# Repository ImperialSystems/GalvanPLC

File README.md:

# GalvanPLC
Galvan PLC es una adaptación de la plataforma Arduino al ámbito industrial, dicho de forma más clara es una imitación de los PLC. El hardware es completamente abierto y está bajo licencia GPL V2. El PCB fue diseñado en KiCAD con solo una capa y pensado para que pueda montarse tanto de forma casera como de forma profesional. Cuenta con 4 salidas digitales del tipo relay, 3 salidas analógicas de 0-5V, 2 entradas analógicas de 10V, 2 entradas analógicas de 4-20mA y 5 entradas digitales de 24V. Puede alimentarse entre 8VDC y 30VDC. Posee conexión USB y comunicación I2C. Es compatible con Soapbox Snap, OpenPLC, LDmicro y Arduino IDE, entre otros.

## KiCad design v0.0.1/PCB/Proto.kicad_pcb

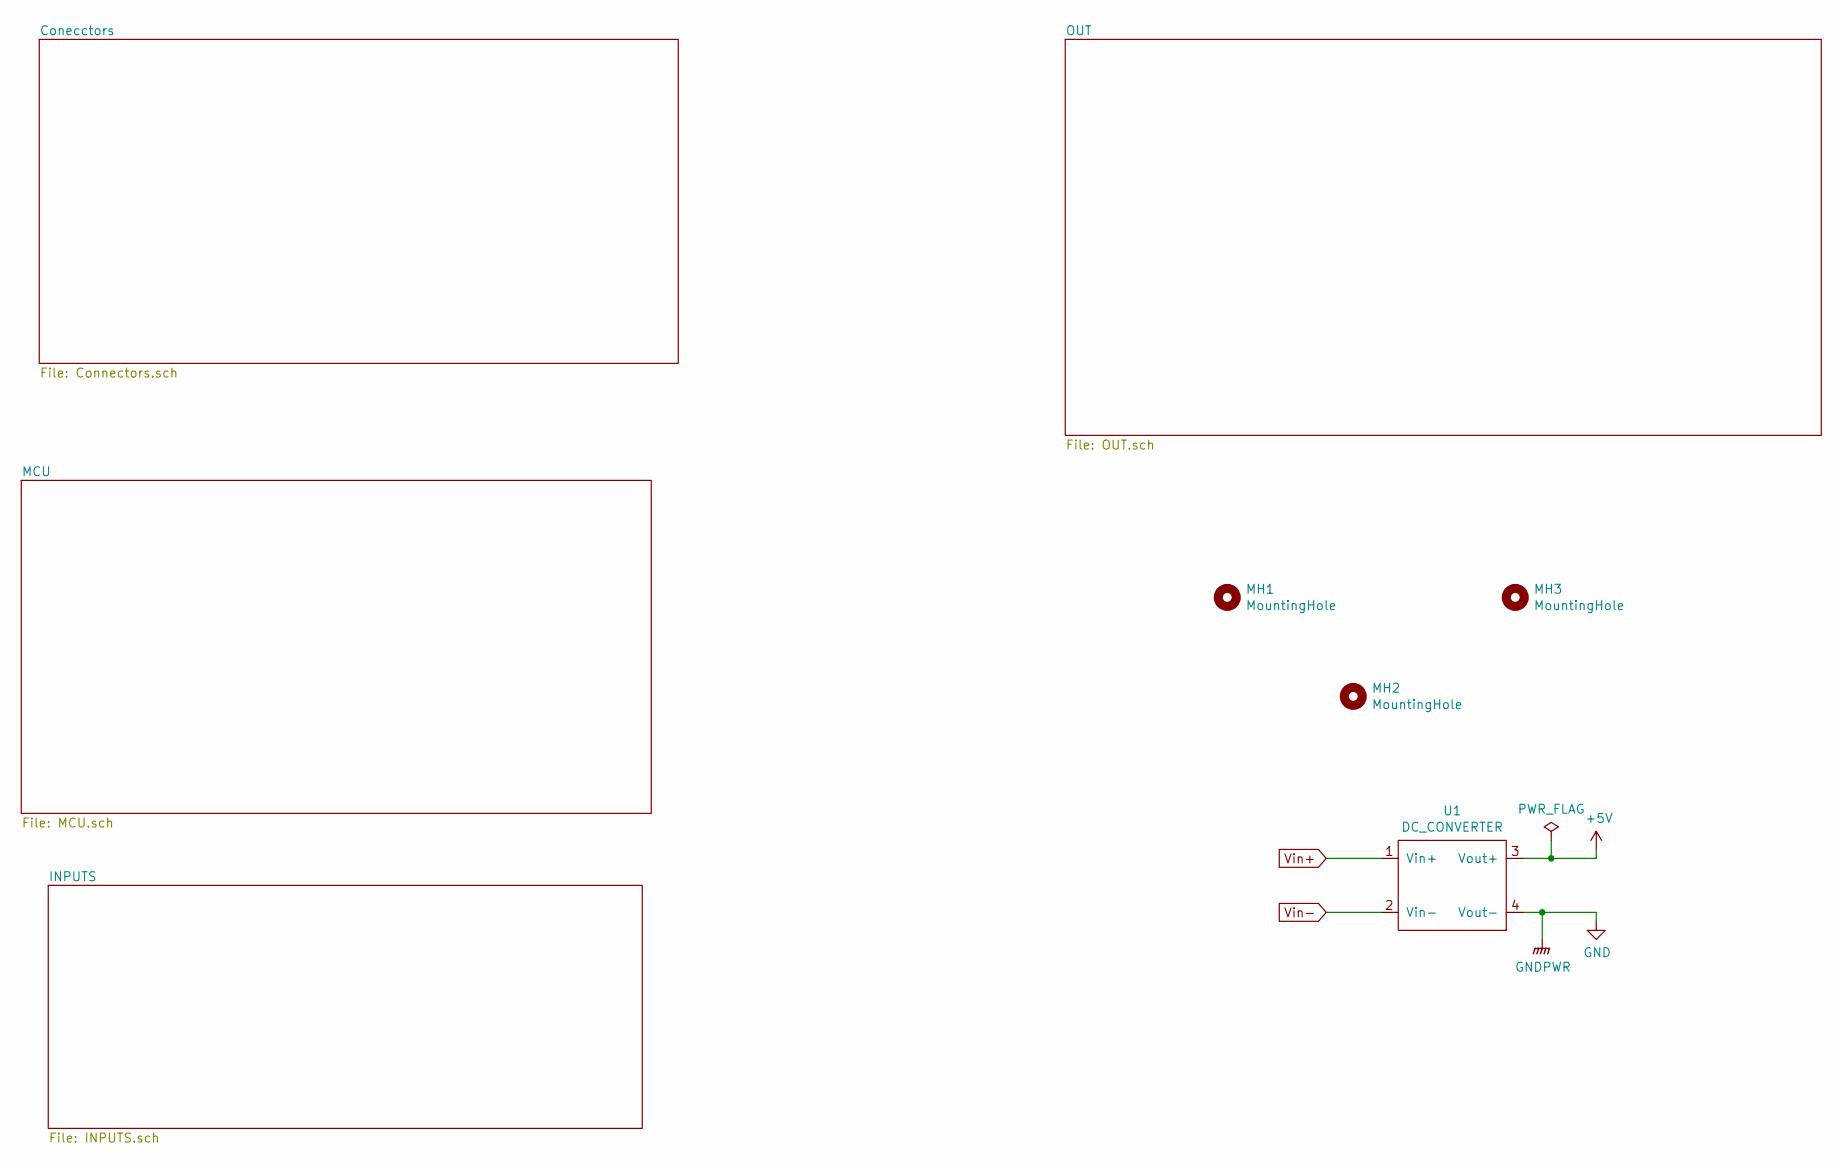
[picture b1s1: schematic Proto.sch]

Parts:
MH1, MH2, MH3: MountingHole; MountingHole_5mm
U1: DC_CONVERTER; Module_LM2596

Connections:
+5V: U1.3 (Vout+); also elsewhere on the board
GND: U1.4 (Vout-); also elsewhere on the board

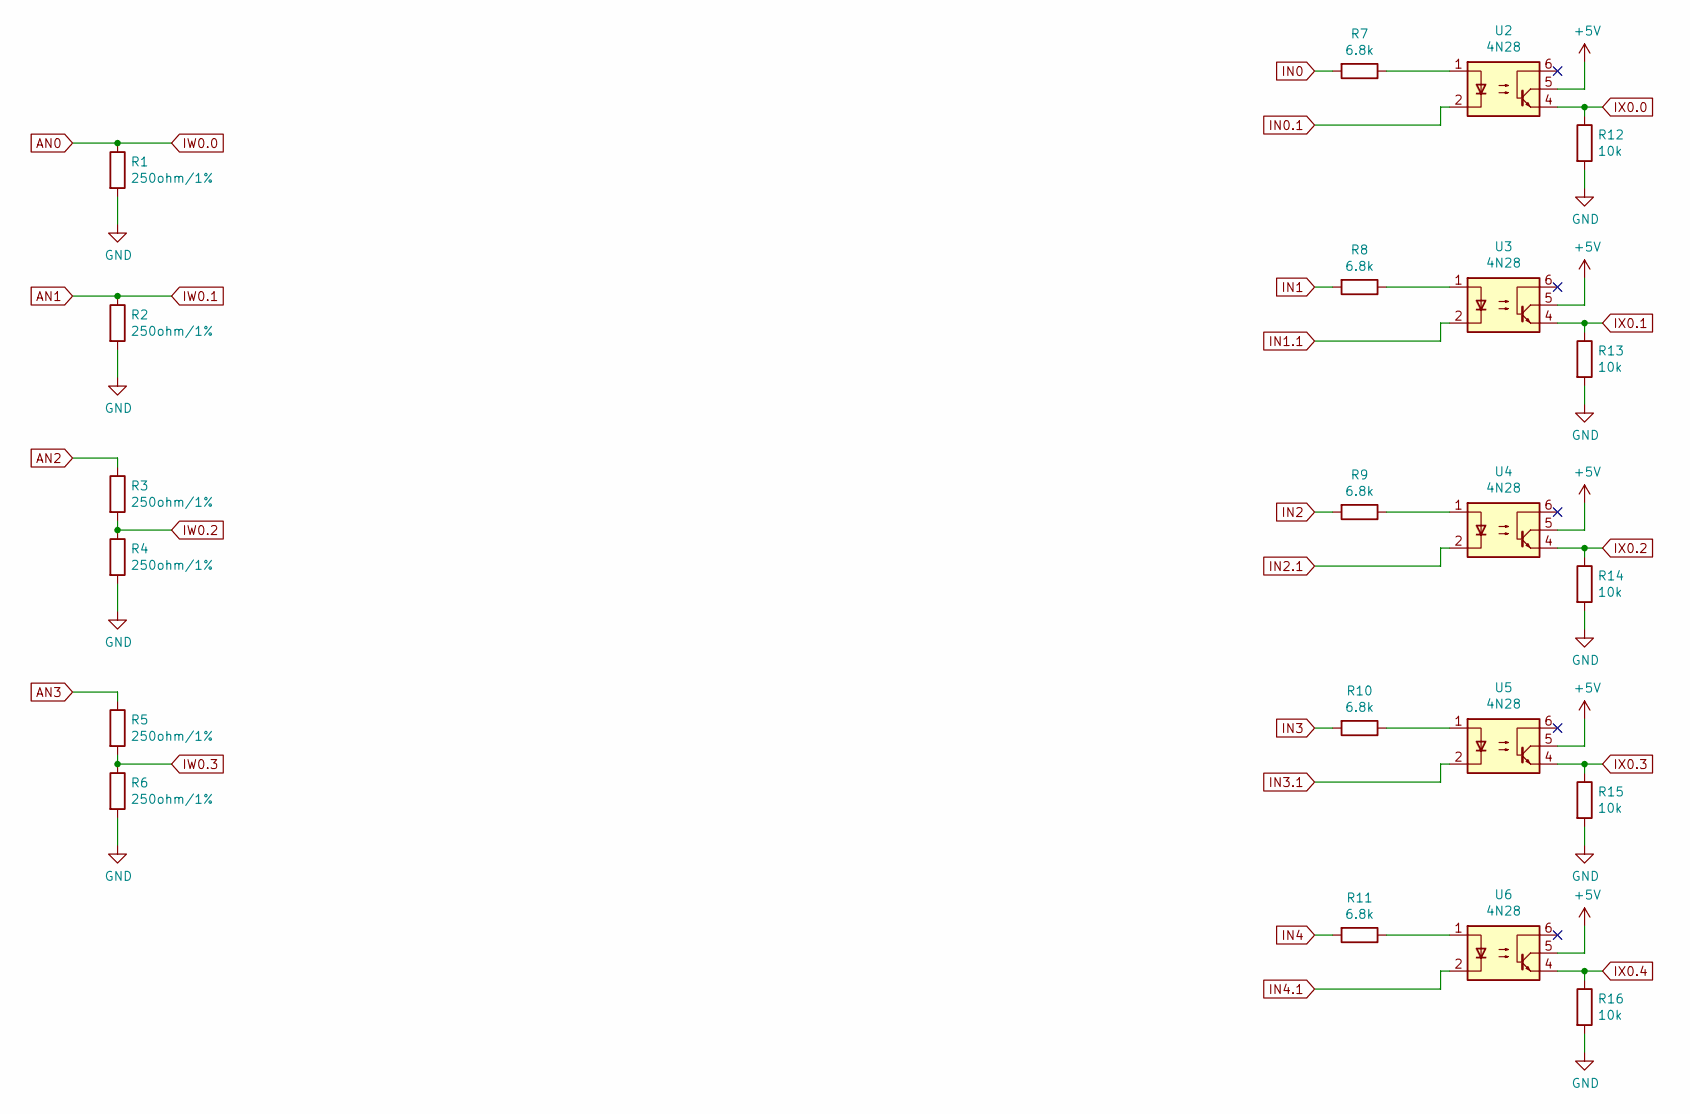
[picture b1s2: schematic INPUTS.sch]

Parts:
R1, R2, R4, R6: 250ohm/1%; R_Axial_DIN0207_L6.3mm_D2.5mm_P15.24mm_Horizontal
R3, R5: 250ohm/1%; R_Axial_DIN0207_L6.3mm_D2.5mm_P10.16mm_Horizontal
R7, R8, R9, R10, R11: 6.8k; R_Axial_DIN0207_L6.3mm_D2.5mm_P15.24mm_Horizontal
R12, R13, R14, R15, R16: 10k; R_Axial_DIN0207_L6.3mm_D2.5mm_P15.24mm_Horizontal
U2, U3, U4, U5, U6: 4N28; DIP-6_W7.62mm

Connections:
+5V: U2.5, U3.5, U4.5, U5.5, U6.5; also elsewhere on the board
AN0: R1.1; also elsewhere on the board
AN1: R2.1; also elsewhere on the board
AN2: R3.1; also elsewhere on the board
AN3: R5.1; also elsewhere on the board
GND: R1.2, R2.2, R4.2, R6.2, R12.2, R13.2, R14.2, R15.2, R16.2; also elsewhere on the board
IN0: R7.2; also elsewhere on the board
IN0.1: U2.2; also elsewhere on the board
IN1: R8.2; also elsewhere on the board
IN1.1: U3.2; also elsewhere on the board
IN2: R9.2; also elsewhere on the board
IN2.1: U4.2; also elsewhere on the board
IN3: R10.2; also elsewhere on the board
IN3.1: U5.2; also elsewhere on the board
IN4: R11.2; also elsewhere on the board
IN4.1: U6.2; also elsewhere on the board
IW0.2: R3.2, R4.1; also elsewhere on the board
IW0.3: R5.2, R6.1; also elsewhere on the board
IX0.0: R12.1, U2.4; also elsewhere on the board
IX0.1: R13.1, U3.4; also elsewhere on the board
IX0.2: R14.1, U4.4; also elsewhere on the board
IX0.3: R15.1, U5.4; also elsewhere on the board
IX0.4: R16.1, U6.4; also elsewhere on the board
unnamed: R7.1, U2.1
unnamed: R8.1, U3.1
unnamed: R9.1, U4.1
unnamed: R10.1, U5.1
unnamed: R11.1, U6.1

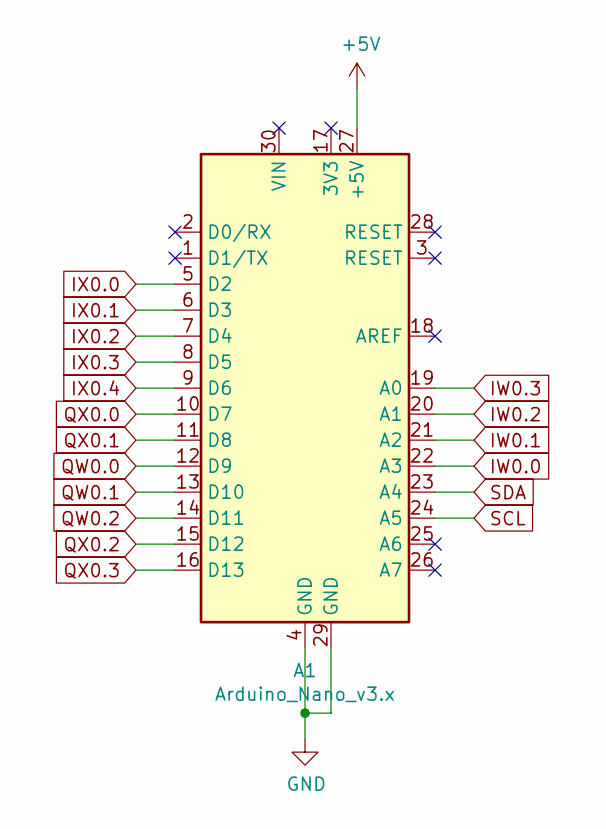
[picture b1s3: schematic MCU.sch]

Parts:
A1: Arduino_Nano_v3.x; Arduino_Nano

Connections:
+5V: A1.27 (+5V); also elsewhere on the board
AN0: A1.22 (A3); also elsewhere on the board
AN1: A1.21 (A2); also elsewhere on the board
GND: A1.4 (GND), A1.29 (GND); also elsewhere on the board
IW0.2: A1.20 (A1); also elsewhere on the board
IW0.3: A1.19 (A0); also elsewhere on the board
IX0.0: A1.5 (D2); also elsewhere on the board
IX0.1: A1.6 (D3); also elsewhere on the board
IX0.2: A1.7 (D4); also elsewhere on the board
IX0.3: A1.8 (D5); also elsewhere on the board
IX0.4: A1.9 (D6); also elsewhere on the board
QW0.0: A1.12 (D9); also elsewhere on the board
QW0.1: A1.13 (D10); also elsewhere on the board
QW0.2: A1.14 (D11); also elsewhere on the board
QX0.0: A1.10 (D7); also elsewhere on the board
QX0.1: A1.11 (D8); also elsewhere on the board
QX0.2: A1.15 (D12); also elsewhere on the board
QX0.3: A1.16 (D13); also elsewhere on the board
SCL: A1.24 (A5); also elsewhere on the board
SDA: A1.23 (A4); also elsewhere on the board

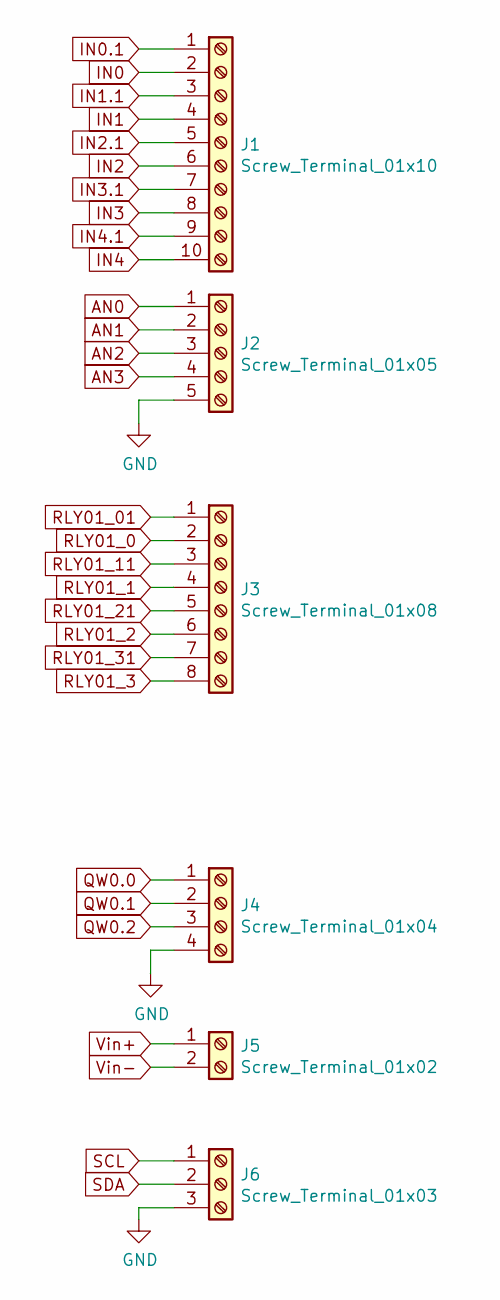
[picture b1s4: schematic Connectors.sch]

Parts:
J1: Screw_Terminal_01x10; TerminalBlock_Phoenix_MKDS-1,5-10-5.08_1x10_P5.08mm_Horizon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
J2: Screw_Terminal_01x05; TerminalBlock_Phoenix_MKDS-1,5-5_1x05_P5.00mm_Horizontal
J3: Screw_Terminal_01x08; TerminalBlock_Phoenix_MKDS-1,5-8_1x08_P5.00mm_Horizontal
J4: Screw_Terminal_01x04; TerminalBlock_Phoenix_MKDS-1,5-4_1x04_P5.00mm_Horizontal
J5: Screw_Terminal_01x02; TerminalBlock_Phoenix_MKDS-1,5-2_1x02_P5.00mm_Horizontal
J6: Screw_Terminal_01x03; TerminalBlock_Phoenix_MKDS-1,5-3_1x03_P5.00mm_Horizontal

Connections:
AN0: J2.1; also elsewhere on the board
AN1: J2.2; also elsewhere on the board
AN2: J2.3; also elsewhere on the board
AN3: J2.4; also elsewhere on the board
GND: J2.5, J4.4, J6.3; also elsewhere on the board
IN0: J1.2; also elsewhere on the board
IN0.1: J1.1; also elsewhere on the board
IN1: J1.4; also elsewhere on the board
IN1.1: J1.3; also elsewhere on the board
IN2: J1.6; also elsewhere on the board
IN2.1: J1.5; also elsewhere on the board
IN3: J1.8; also elsewhere on the board
IN3.1: J1.7; also elsewhere on the board
IN4: J1.10; also elsewhere on the board
IN4.1: J1.9; also elsewhere on the board
QW0.0: J4.1; also elsewhere on the board
QW0.1: J4.2; also elsewhere on the board
QW0.2: J4.3; also elsewhere on the board
RLY01_0: J3.2; also elsewhere on the board
RLY01_01: J3.1; also elsewhere on the board
RLY01_1: J3.4; also elsewhere on the board
RLY01_2: J3.6; also elsewhere on the board
RLY01_3: J3.8; also elsewhere on the board
RLY01_11: J3.3; also elsewhere on the board
RLY01_21: J3.5; also elsewhere on the board
RLY01_31: J3.7; also elsewhere on the board
SCL: J6.1; also elsewhere on the board
SDA: J6.2; also elsewhere on the board

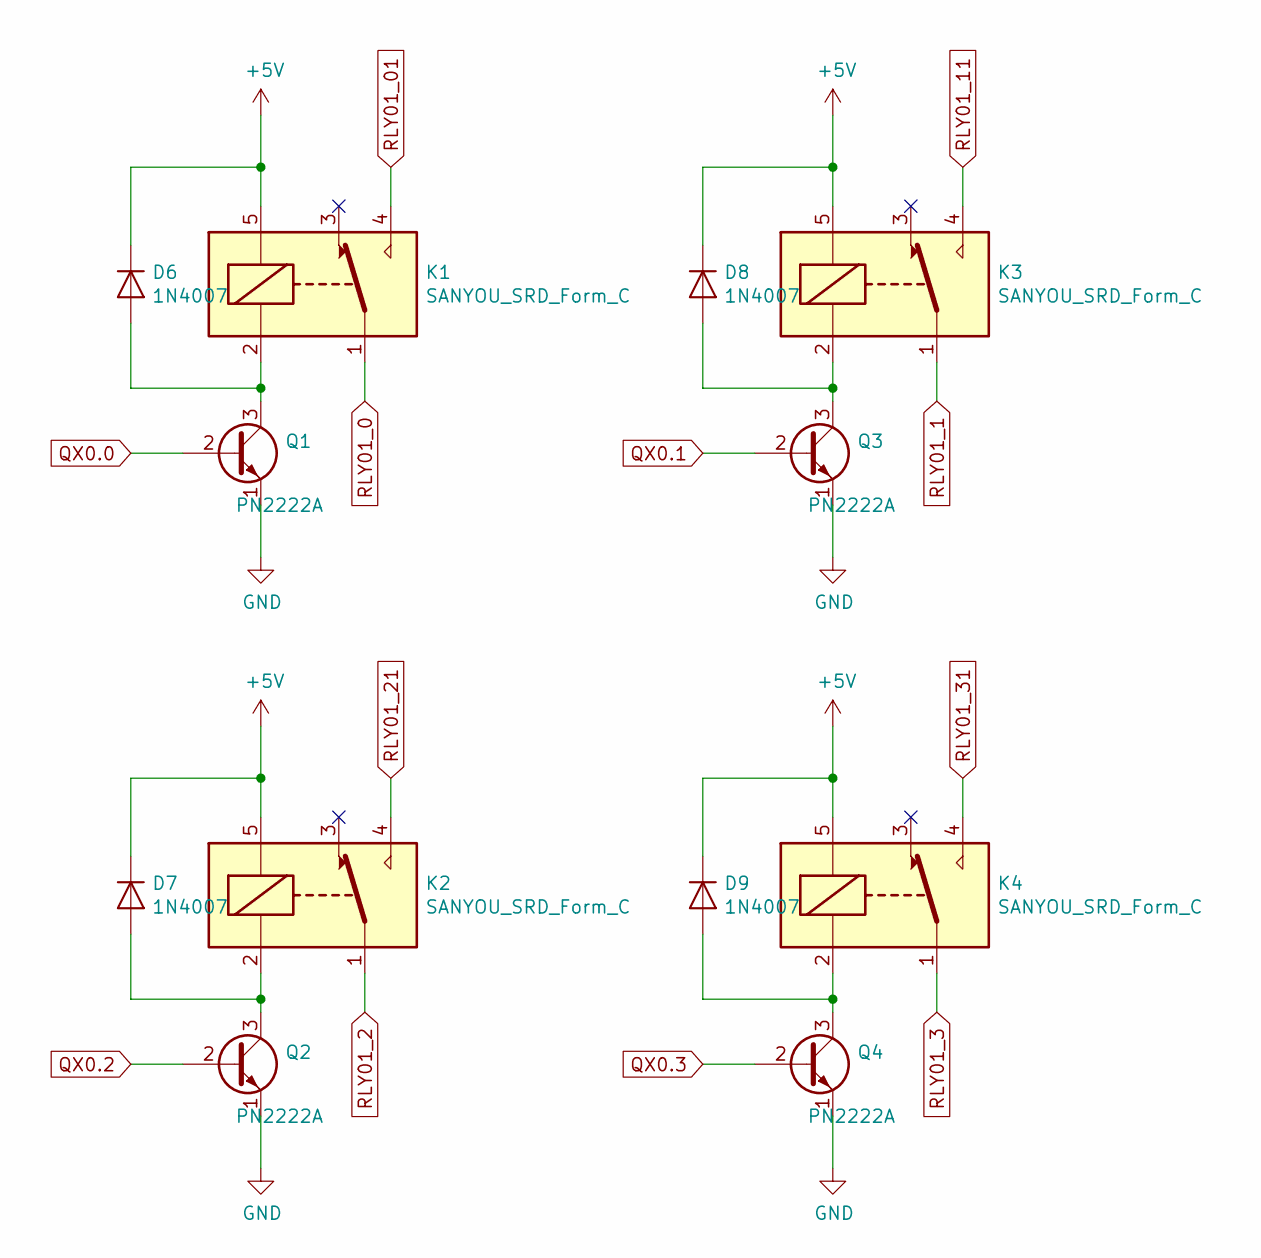
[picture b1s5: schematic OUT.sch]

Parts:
D6, D7, D8, D9: 1N4007; D_DO-41_SOD81_P12.70mm_Horizontal
K1, K2, K3, K4: SANYOU_SRD_Form_C; Relay_SPDT_SANYOU_SRD_Series_Form_C
Q1, Q2, Q3, Q4: PN2222A; TO-92_HandSolder

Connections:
+5V: D6.1 (K), D7.1 (K), D8.1 (K), D9.1 (K), K1.5, K2.5, K3.5, K4.5; also elsewhere on the board
GND: Q1.1 (E), Q2.1 (E), Q3.1 (E), Q4.1 (E); also elsewhere on the board
unnamed: D6.2 (A), K1.2, Q1.3 (C)
unnamed: D7.2 (A), K2.2, Q2.3 (C)
unnamed: D8.2 (A), K3.2, Q3.3 (C)
unnamed: D9.2 (A), K4.2, Q4.3 (C)
QX0.0: Q1.2 (B); also elsewhere on the board
QX0.1: Q3.2 (B); also elsewhere on the board
QX0.2: Q2.2 (B); also elsewhere on the board
QX0.3: Q4.2 (B); also elsewhere on the board
RLY01_0: K1.1; also elsewhere on the board
RLY01_01: K1.4; also elsewhere on the board
RLY01_1: K3.1; also elsewhere on the board
RLY01_2: K2.1; also elsewhere on the board
RLY01_3: K4.1; also elsewhere on the board
RLY01_11: K3.4; also elsewhere on the board
RLY01_21: K2.4; also elsewhere on the board
RLY01_31: K4.4; also elsewhere on the board

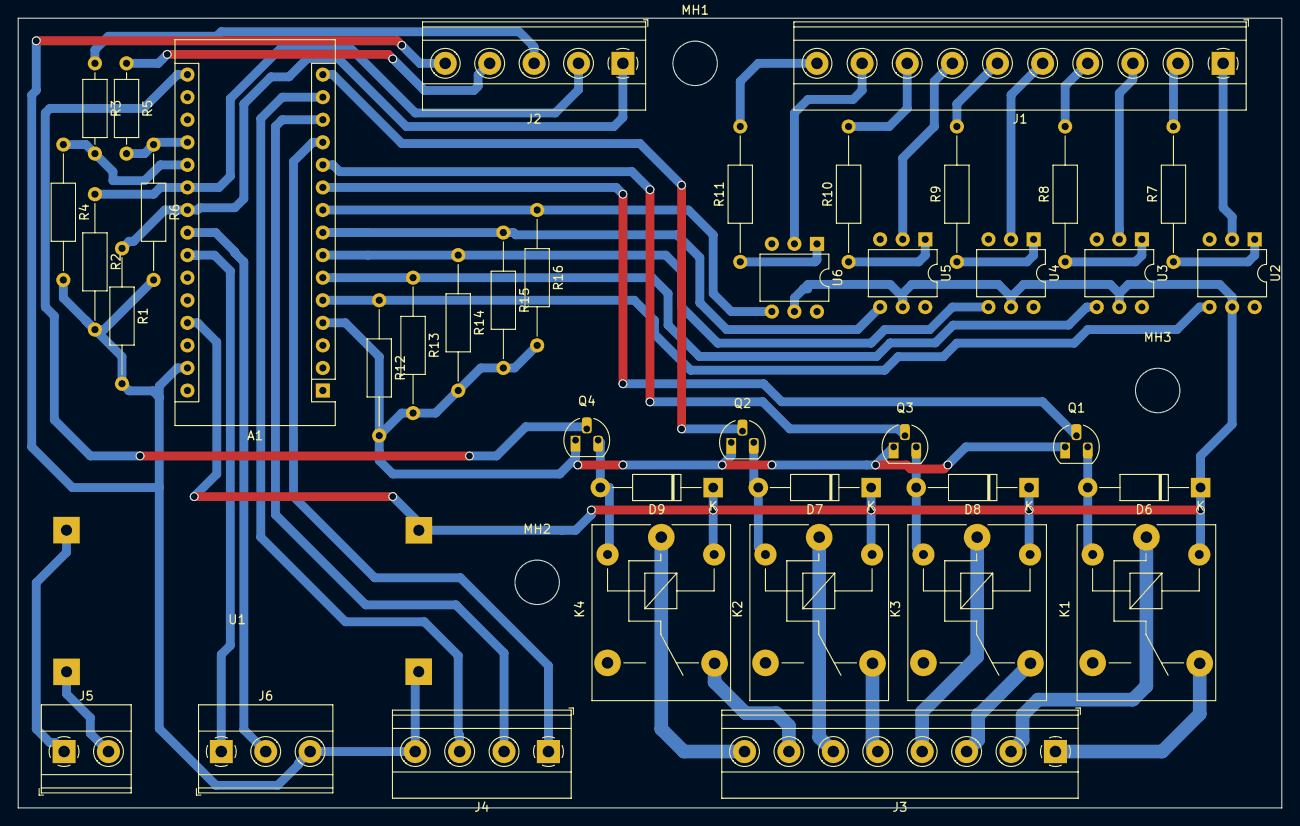
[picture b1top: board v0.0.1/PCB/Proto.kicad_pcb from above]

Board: 2 copper layers, 142.2 x 88.9 mm, 44 parts (0 on the bottom side), 49 nets.

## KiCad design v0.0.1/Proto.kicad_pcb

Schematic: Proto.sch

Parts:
10k1, 10k2, 10k3, 10k4: R; R_Axial_DIN0207_L6.3mm_D2.5mm_P10.16mm_Horizontal
C1, C2: CP1_Small; CP_Radial_D10.0mm_P5.00mm
D1: D_Zener; D_A-405_P10.16mm_Horizontal
D2: D; D_A-405_P10.16mm_Horizontal
D3, D4, D5, D6: 20v; D_A-405_P2.54mm_Vertical_KathodeUp
J1: Arduino_Header; arduino_header
L1: L; C_Disc_D9.0mm_W5.0mm_P10.00mm
P1, P2, P6, P7: CONN_01X08; mstba_2,5%2f8-g-5,08
P3: CONN_01X02; TerminalBlock_Pheonix_MKDS1.5-2pol
P4: CONN_01X03; Pin_Header_Straight_1x03_Pitch2.54mm
Q2, Q3, Q4: IRF540N; TO-220_Vertical
R1, R2, R3, R4, R5, R6, R7, R8: R; R_Axial_DIN0309_L9.0mm_D3.2mm_P12.70mm_Horizontal
R9, R10, R11, R12, R13, R14, R15, R16: 10k; R_Axial_DIN0207_L6.3mm_D2.5mm_P10.16mm_Horizontal
R17: 6.3k; R_Axial_DIN0207_L6.3mm_D2.5mm_P10.16mm_Horizontal
R18: 2.2k; R_Axial_DIN0207_L6.3mm_D2.5mm_P10.16mm_Horizontal
R19, R20, R21, R22: 330; R_Axial_DIN0207_L6.3mm_D2.5mm_P10.16mm_Horizontal
RLY3, RLY4, RLY7, RLY8: RELAY_V23101-D1; relay_V23101-D1
U1: TL2575; TO-220-5_Pentawatt_Multiwatt-5_Horizontal_StaggeredType1
U2, U3, U4, U5: TLP627-2; DIP-8_W7.62mm_LongPads
U7, U8, U9: 4N25; DIP-6_W7.62mm

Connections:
+5V: C1.1, C2.1, J1.5, L1.2, R17.2, U2.6, U2.8, U3.6, U3.8, U4.6, U4.8, U5.6, U5.8
GND: C1.2, C2.2, D1.2, J1.6, J1.7, J1.29, P3.1, P4.3, R9.1, R10.1, R11.1, R12.1, R13.1, R14.1, R15.1, R16.1, R18.1, RLY3.2, RLY4.2, RLY7.2, RLY8.2, U1.3, U1.5, U7.2, U8.2, U9.2; also elsewhere on the board
IN1: J1.12, R9.2, U2.7
IN2: J1.11, R10.2, U2.5
IN3: J1.10, R11.2, U3.7
IN4: J1.9, R12.2, U3.5
IN5: J1.17, R13.2, U4.7
IN6: J1.18, R14.2, U4.5
IN7: J1.19, R15.2, U5.7
IN8: J1.20, R16.2, U5.5
unnamed 10: 10k1.1; also elsewhere on the board
unnamed: 10k2.1, Q2.1 (G), U7.4
unnamed: 10k3.1, Q3.1 (G), U8.4
unnamed: 10k4.1, Q4.1 (G), U9.4
unnamed: D1.1, L1.1, U1.2
unnamed: D2.1, U1.1
unnamed: D2.2, P3.2
unnamed: J1.31, P4.2
unnamed: J1.32, P4.1
unnamed: P1.1, U3.4
unnamed: P1.2, R4.2
unnamed: P1.3, U3.2
unnamed: P1.4, R3.2
unnamed: P1.5, U2.4
unnamed: P1.6, R2.2
unnamed: P1.7, U2.2
unnamed: P1.8, R1.2
unnamed: P2.1, U5.4
unnamed: P2.2, R8.2
unnamed: P2.3, U5.2
unnamed: P2.4, R7.2
unnamed: P2.5, U4.4
unnamed: P2.6, R6.2
unnamed: P2.7, U4.2
unnamed: P2.8, R5.2
unnamed: R1.1, U2.1
unnamed: R2.1, U2.3
unnamed: R3.1, U3.1
unnamed: R4.1, U3.3
unnamed: R5.1, U4.1
unnamed: R6.1, U4.3
unnamed: R7.1, U5.1
unnamed: R8.1, U5.3
unnamed: R17.1, R18.2, U1.4
unnamed 53: R19.1; also elsewhere on the board
unnamed: R20.1, U7.1
unnamed: R21.1, U8.1
unnamed: R22.1, U9.1
Q1: J1.28, RLY4.11
Q2: J1.27, RLY8.11
Q3: J1.26, R19.2
Q4: J1.25, R21.2
Q5: J1.24, R20.2
Q6: J1.23, RLY3.11
Q7: J1.22, RLY7.11
Q8: J1.21, R22.2
q1.1: P6.8, RLY4.7
q1.2: P6.7, RLY4.12
q2.1: P6.6, RLY8.7
q2.2: P6.5, RLY8.12
q3.1: P6.4, RLY3.7
q3.2: P6.3, RLY3.12
q4.1: P6.2, RLY7.7
q4.2: P6.1, RLY7.12
q5.1: D3.1, P7.8; also elsewhere on the board
q5.2: 10k1.2, D3.2, P7.7; also elsewhere on the board
q6.1: D5.1, P7.6, Q3.2 (D), U8.5
q6.2: 10k3.2, D5.2, P7.5, Q3.3 (S)
q7.1: D4.1, P7.4, Q2.2 (D), U7.5
q7.2: 10k2.2, D4.2, P7.3, Q2.3 (S)
q8.1: D6.1, P7.2, Q4.2 (D), U9.5
q8.2: 10k4.2, D6.2, P7.1, Q4.3 (S)

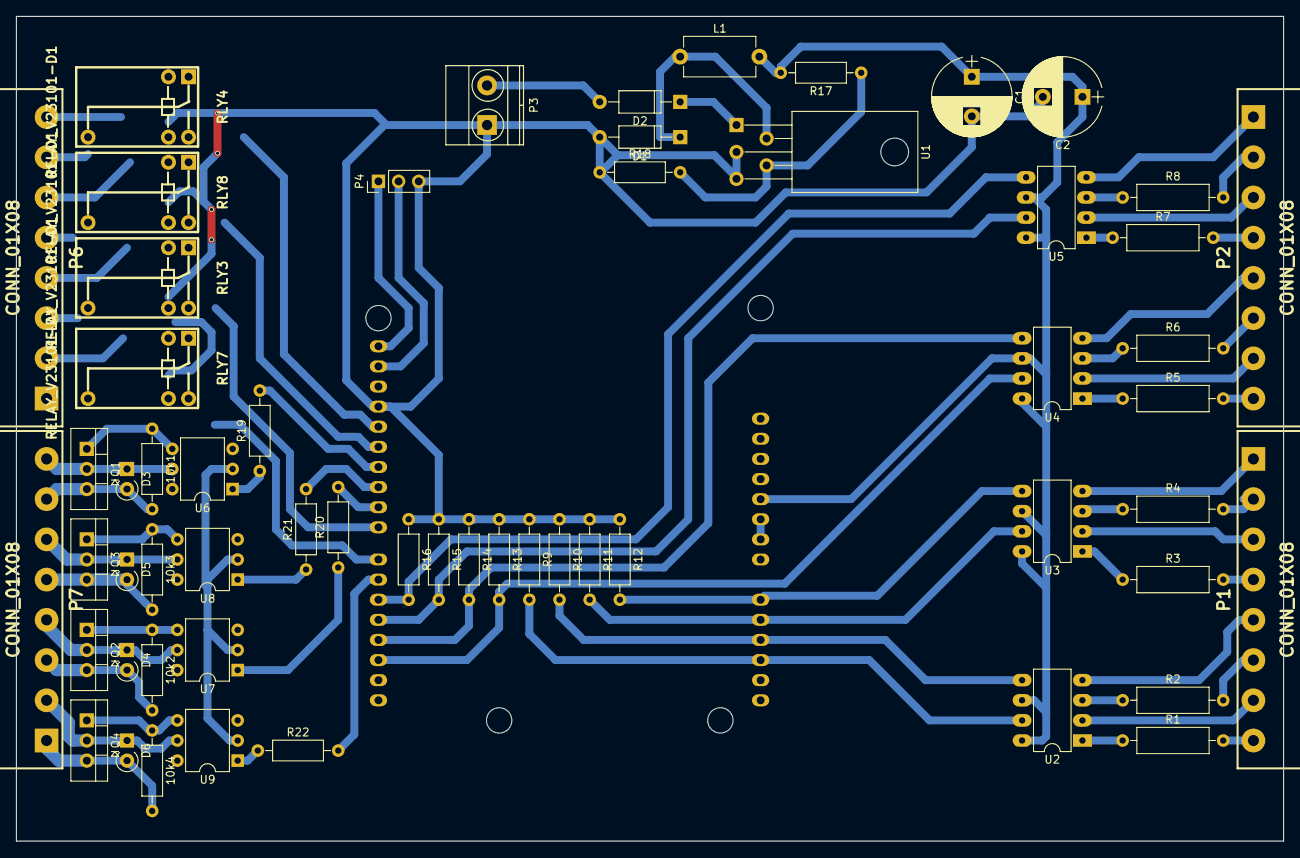
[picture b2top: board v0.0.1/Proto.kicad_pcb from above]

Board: 2 copper layers, 160.0 x 104.1 mm, 59 parts (1 on the bottom side), 72 nets.

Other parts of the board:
Q1: IRF540N; TO-220_Vertical
U6: 4N25; DIP-6_W7.62mm

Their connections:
GND: U6.2; also elsewhere on the board
unnamed 10: Q1.1, U6.4; also elsewhere on the board
unnamed 53: U6.1; also elsewhere on the board
q5.1: Q1.2, U6.5; also elsewhere on the board
q5.2: Q1.3; also elsewhere on the board

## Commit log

2019-09-23 Update README.md
    Se agrega pequeña descripción, se planean mejoras en ella.
2019-10-16 fixed wrong files
